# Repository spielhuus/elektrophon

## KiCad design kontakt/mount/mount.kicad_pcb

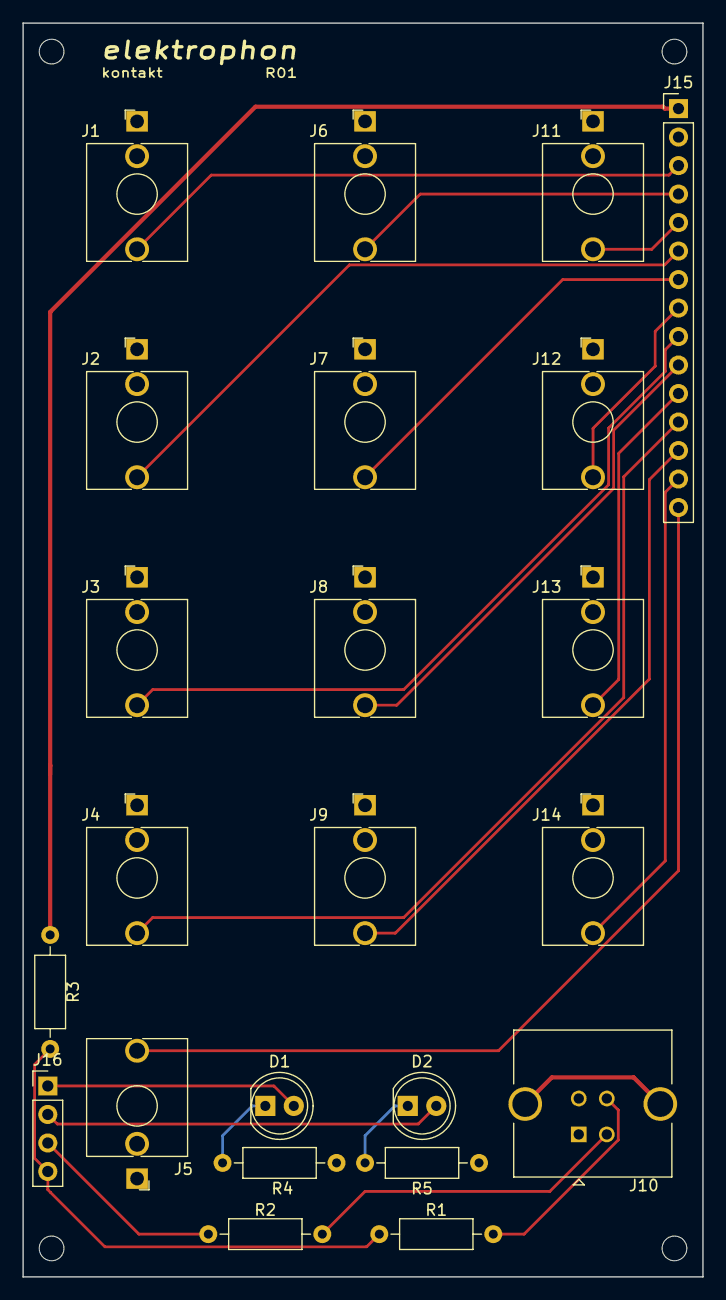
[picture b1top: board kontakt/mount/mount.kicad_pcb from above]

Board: 2 copper layers, 60.6 x 111.8 mm, 27 parts (0 on the bottom side), 23 nets.

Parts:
D1, D2: LED; LED_D5.0mm
H1, H2, H3, H4: MountingHole; MountingHole_2.2mm_M2
J1, J2, J3, J4, J5, J6, J7, J8, J9, J11, J12, J13, J14: INPUT; Jack_3.5mm_WQP-PJ398SM_Vertical
J10: USB_B; USB_B_TE_5787834_Vertical
J15: Conn_01x15_Male; PinHeader_1x15_P2.54mm_Vertical
J16: Conn_01x04_Male; PinHeader_1x04_P2.54mm_Vertical
R1, R2: 20; R_Axial_DIN0207_L6.3mm_D2.5mm_P10.16mm_Horizontal
R3: 1k5; R_Axial_DIN0207_L6.3mm_D2.5mm_P10.16mm_Horizontal
R4, R5: 56; R_Axial_DIN0207_L6.3mm_D2.5mm_P10.16mm_Horizontal

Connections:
+5V: J15.1, R3.2
/PA11: J16.3, R2.1
/PA12: J16.4, R1.1, R3.1
GND: J1.S, J2.S, J3.S, J4.S, J5.S, J6.S, J7.S, J8.S, J9.S, J10.4, J11.S, J12.S, J13.S, J14.S, J15.2, R4.2, R5.2
LED_ACTIVITY: D1.2, J16.1
LED_CONNECT: D2.2, J16.2
unnamed: D1.1, R4.1
unnamed: D2.1, R5.1
unnamed: J10.2, R2.2
unnamed: J10.3, R1.2
Note_1: J1.T, J15.3
Note_2: J6.T, J15.4
Note_3: J11.T, J15.5
OUT_CLOCK: J5.T, J15.15
OUT_TRIGGER_1: J4.T, J15.12
OUT_TRIGGER_2: J9.T, J15.13
OUT_TRIGGER_3: J14.T, J15.14
PITCH_BEND_1: J3.T, J15.9
PITCH_BEND_2: J8.T, J15.10
PITCH_BEND_3: J13.T, J15.11
Velocity_1: J2.T, J15.6
Velocity_2: J7.T, J15.7
Velocity_3: J12.T, J15.8

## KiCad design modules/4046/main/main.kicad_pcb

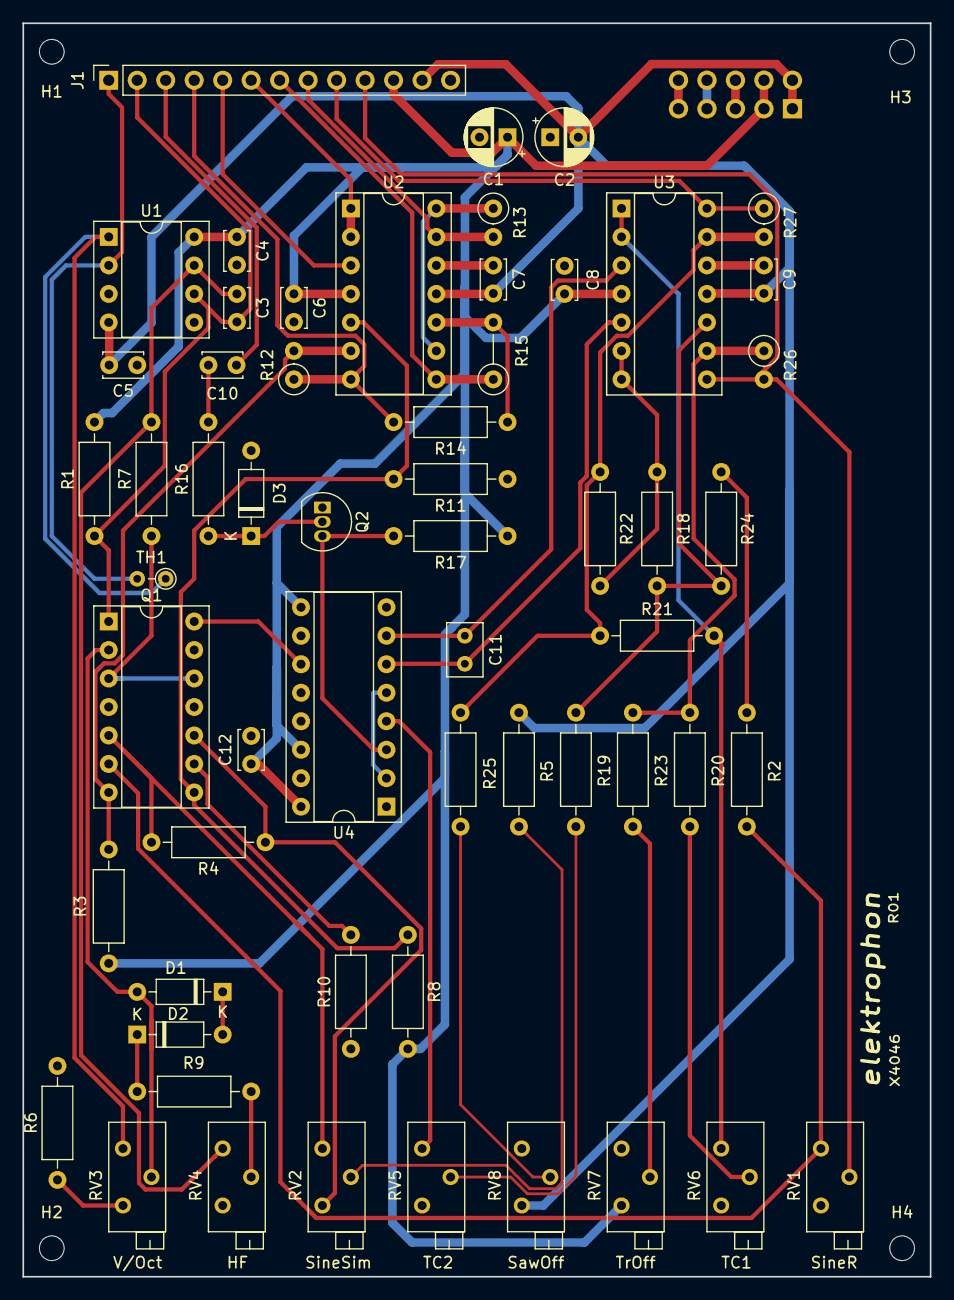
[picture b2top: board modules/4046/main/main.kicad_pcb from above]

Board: 2 copper layers, 80.9 x 111.8 mm, 63 parts (1 on the bottom side), 48 nets.

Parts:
C1, C2: 10u; CP_Radial_D5.0mm_P2.50mm
C3: 100p; C_Disc_D3.4mm_W2.1mm_P2.50mm
C4, C5, C6, C7, C8, C9, C12: 0.1u; C_Disc_D3.4mm_W2.1mm_P2.50mm
C10: 470p; C_Disc_D3.4mm_W2.1mm_P2.50mm
C11: 0.01u (Mylar); C_Rect_L4.6mm_W3.0mm_P2.50mm_MKS02_FKP02
D1, D2, D3: 1N4148; D_DO-35_SOD27_P7.62mm_Horizontal
H1, H2, H3, H4: MountingHole; MountingHole_2.2mm_M2
J1: Conn_01x13_Female; PinSocket_1x13_P2.54mm_Vertical
J2: IDC Header; IDC-Header_2x05_P2.54mm_Vertical
Q1: THAT300; DIP-14_W7.62mm_Socket
Q2: 2N3904; TO-92_Inline
R1: 1M5; R_Axial_DIN0207_L6.3mm_D2.5mm_P10.16mm_Horizontal
R2, R14: 2k2; R_Axial_DIN0207_L6.3mm_D2.5mm_P10.16mm_Horizontal
R3, R8, R9, R11: 10k; R_Axial_DIN0207_L6.3mm_D2.5mm_P10.16mm_Horizontal
R4, R6: 390; R_Axial_DIN0207_L6.3mm_D2.5mm_P10.16mm_Horizontal
R5: 18k; R_Axial_DIN0207_L6.3mm_D2.5mm_P10.16mm_Horizontal
R7: 12k; R_Axial_DIN0207_L6.3mm_D2.5mm_P10.16mm_Horizontal
R10: 2.2k; R_Axial_DIN0207_L6.3mm_D2.5mm_P10.16mm_Horizontal
R12: 10k; R_Axial_DIN0207_L6.3mm_D2.5mm_P2.54mm_Vertical
R13: 120k; R_Axial_DIN0207_L6.3mm_D2.5mm_P2.54mm_Vertical
R15: 2.2M; R_Axial_DIN0207_L6.3mm_D2.5mm_P5.08mm_Vertical
R16, R19: 100k; R_Axial_DIN0207_L6.3mm_D2.5mm_P10.16mm_Horizontal
R17: 4k7; R_Axial_DIN0207_L6.3mm_D2.5mm_P10.16mm_Horizontal
R18, R21, R22: 75k; R_Axial_DIN0207_L6.3mm_D2.5mm_P10.16mm_Horizontal
R20: 33k; R_Axial_DIN0207_L6.3mm_D2.5mm_P10.16mm_Horizontal
R23, R25: 220k; R_Axial_DIN0207_L6.3mm_D2.5mm_P10.16mm_Horizontal
R24: 120k; R_Axial_DIN0207_L6.3mm_D2.5mm_P10.16mm_Horizontal
R26, R27: 100k; R_Axial_DIN0207_L6.3mm_D2.5mm_P2.54mm_Vertical
RV1, RV4, RV5, RV6, RV7, RV8: 100k; Potentiometer_Bourns_3296Z_Horizontal
RV2: 50k; Potentiometer_Bourns_3296Z_Horizontal
RV3: 100; Potentiometer_Bourns_3296Z_Horizontal
TH1: 2k +3500ppm/°C PTC; R_Axial_DIN0204_L3.6mm_D1.6mm_P2.54mm_Vertical
U1: LF442; DIP-8_W7.62mm_Socket
U2, U3: TL074; DIP-14_W7.62mm_Socket
U4: 4046; DIP-16_W7.62mm_Socket

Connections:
+5V: J2.9, J2.10
+15V: C1.1, C4.1, C6.1, C8.1, C12.1, J1.11, J2.3, J2.4, R1.2, R3.2, R8.2, R17.1, RV7.3, U1.8, U2.4, U3.4, U4.9, U4.14, U4.16
-15V: C2.2, C5.2, C7.2, C9.2, J1.12, J2.1, J2.2, R5.1, RV8.3, U1.4, U2.11, U3.11
/CI_1: C11.2, U3.5, U4.6
/CI_2: C11.1, U3.3, U4.7
/CV: Q1.14, U4.11
/EXP_FM: J1.1, TH1.2, U1.2
/HARD_SYNC: C10.2, J1.3
/LIN_FM: C3.2, J1.2, Q1.1, R1.1, U1.6
/PULSE: J1.7, R15.1, U2.8
/PWM: J1.8, R13.2, U2.13
/RAMPOID: J1.6, U2.1, U2.2
/SAW: J1.9, R27.1, U3.14
/SINE: J1.4, R12.1, R14.2, U2.7
/SKEW: J1.5, U2.3
/SYNC: Q2.3, R17.2, U4.3
/TRIANGLE: J1.10, R26.2, RV1.2, U3.8
/VCO_OUT: RV5.1, U4.4
GND: C1.2, C2.1, C4.2, C5.1, C6.2, C7.1, C8.2, C9.1, C12.2, D3.2, J1.13, J2.5, J2.6, J2.7, J2.8, Q1.13, Q2.1, R2.1, R6.2, R10.1, R11.1, R24.1, RV5.3, RV6.3, RV7.1, RV8.1, U1.3, U1.5, U2.12, U3.12, U4.8
unnamed: C3.1, R7.2, RV4.1, U1.7
unnamed: C10.1, R16.2
unnamed: D1.1, D2.2
unnamed: D1.2, Q1.2, RV3.2
unnamed: D2.1, R9.1
unnamed: D3.1, Q2.2, R16.1
unnamed: Q1.5, R4.2, RV2.1
unnamed: Q1.6, R2.2, RV1.1
unnamed: Q1.7, R3.1, R12.2, U2.6
unnamed: Q1.8, R8.1, R11.2, U2.5
unnamed: Q1.9, R10.2
unnamed: Q1.10, R4.1, RV2.3
unnamed: Q1.3, Q1.12, R7.1
unnamed: R5.2, RV2.2
unnamed: R6.1, RV3.3
unnamed: R9.2, RV4.2
unnamed: R13.1, U2.9, U2.14
unnamed: R14.1, R15.2, U2.10
unnamed: R18.1, R22.2, U3.6, U3.7
unnamed: R18.2, R19.2, R24.2, U3.10
unnamed: R19.1, RV5.2
unnamed: R20.1, RV6.2
unnamed: R20.2, R23.1, R26.1, U3.9
unnamed: R21.1, R22.1, R25.1, R27.2, U3.13
unnamed: R21.2, RV6.1, U3.1, U3.2
unnamed: R23.2, RV7.2
unnamed: R25.2, RV8.2
unnamed: RV3.1, TH1.1, U1.1
unnamed: U4.2, U4.5

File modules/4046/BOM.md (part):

## BOM: X4046

### main panel

For the main panel the two integrated circuits the CD4046 and the THAT300 are not so easy to get. The 4046 shall not be from Texas Instruments. It is reported that the chip from TI is hard or impossible to tune. This is sad, becuase this is the part you can find everywhere. You can get the one from National Semiconductor (CD4046), Motorola (MC14046) or Philips (HEF4046). The THAT part is rather expensive, but can be ordered from china. 


| Qty | Reference(s)                  | Value              | Description                                                                                                     | 
|-----|-------------------------------|--------------------|---------------------------------------------------------------------------------------------------------------| 
| 2   | C1, C2                      | 10u                | Electrolytic Capacitors - Radial (D:5.0mm, P:2.50mm)                                                        | 
| 1   | C3                            | 100p               | Ceramic Capacitors (L:4mm, P:2.50mm)                                                                        | 
| 7   | C4, C5, C6, C7, C8, C9, C12 | 0.1u               | Ceramic Capacitors (L:4mm, P:2.50mm)                                                                        | 
| 1   | C10                           | 470p               | Ceramic Capacitors (L:4mm, P:2.50mm)                                                                        | 
| 1   | C11                           | 0.01u              | Capacitor Polyethylene Terephthalate (PET) (L:4.6mm, W:2.5mm, P=2.5mm)                                      | 
| 3   | D1, D2, D3                  | 1N4148             | Diode                                                                                                         | 
| 1   | J1                            | 13 Pins / 1 Row    | Pin Socket Connector (P2.54mm)                                                                                | 
| 1   | J2                            | 10 Pins / 2 Rows   | PCB IDC Socket (P2.54mm, Vertical)                                                                          | 
| 1   | Q1                            | THAT300            | [Matched Transistor Array](https://spielhuus.github.io/elektrophon/datasheet/THAT_300-S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   | 
| 1   | Q2                            | 2N3904             | [Transistors NPN](https://spielhuus.github.io/elektrophon/datasheet/2N3903.pdf)                               | 
| 1   | R1                            | 1M5                | Resistor (L:6.3mm, D:2.5mm)                                                                                 | 
| 1   | R2                            | 2k2                | Resistor (L:6.3mm, D:2.5mm)                                                                                 | 
| 4   | R3, R8, R9, R11             | 10k                | Resistor (L:6.3mm, D:2.5mm)                                                                                 | 
| 2   | R4, R6                      | 390                | Resistor (L:6.3mm, D:2.5mm)                                                                                 | 
| 1   | R5                            | 18k                | Resistor (L:6.3mm, D:2.5mm)                                                                                 | 
| 1   | R7                            | 12k                | Resistor (L:6.3mm, D:2.5mm)                                                                                 | 
| 2   | R10, R14                    | 2.2k               | Resistor (L:6.3mm, D:2.5mm)                                                                                 | 
| 1   | R12                           | 10k                | Resistor (L:6.3mm, D:2.5mm)                                                                                 | 
| 1   | R13                           | 120k               | Resistor (L:6.3mm, D:2.5mm)                                                                                 | 
| 1   | R15                           | 2.2M               | Resistor (L:6.3mm, D:2.5mm)                                                                                 | 
| 2   | R16, R19                    | 100k               | Resistor (L:6.3mm, D:2.5mm)                                                                                 | 
| 1   | R17                           | 4k7                | Resistor (L:6.3mm, D:2.5mm)                                                                                 | 
| 3   | R18, R21, R22               | 75k                | Resistor (L:6.3mm, D:2.5mm)                                                                                 | 
| 1   | R20                           | 33k                | Resistor (L:6.3mm, D:2.5mm)                                                                                 | 
| 2   | R23, R25                    | 220k               | Resistor (L:6.3mm, D:2.5mm)                                                                                 | 
| 1   | R24                           | 120k               | Resistor (L:6.3mm, D:2.5mm)                                                                                 | 
| 2   | R26, R27                    | 100k               | Resistor (L:6.3mm, D:2.5mm)                                                                                 | 
| 2   | RV1, RV4                    | 100k               | Trimpotentiometer (Bourns 3296Z)                                                                              | 
| 1   | RV2                           | 50k                | Trimpotentiometer (Bourns 3296Z)                                                                              | 
| 1   | RV3                           | 100                | Trimpotentiometer (Bourns 3296Z)                                                                              | 
| 3   | RV5, RV6, RV7               | 100k               | Trimpotentiometer (Bourns 3296Z)                                                                              | 
| 1   | RV8                           | 100k             | Trimpotentiometer (Bourns 3296Z)                                                                              | 
| 1   | TH1                           | 2k | PTC (Positive Temperature Coefficient) Thermistors                                                            | 
| 1   | U1                            | LF442              | [Dual Low Power JFETInput Operational Amplifier](https://spielhuus.github.io/elektrophon/datasheet/LF442.pdf) | 
| 2   | U2, U3                      | TL074              | [Low-Noise JFET-Input Operational Amplifiers](https://spielhuus.github.io/elektrophon/datasheet/TL07xx.pdf)   | 
| 1   | U4                            | 4046               | [CMOS Phase Locked Loop](https://spielhuus.github.io/elektrophon/datasheet/cd4046b.pdf)                       | 

### mount panel                                            

| Qty | Reference(s)                              | Value           | Description                                                             | 
|-----|-------------------------------------------|-----------------|-------------------------------------------------------------------------| 
| 1   | C1                                        | 0.22u           | Capacitors Polyethylene Terephthalate (PET) (L4.6mm, W3.0mm, P2.50mm) | 
| 10  | J1, J2, J3, J4, J5, J6, J7, J8, J9, J10 | Mono            | [Audio Jack 3.5mm (PJ398SM, Vertical)](https://www.thonk.co.uk/shop/3-5mm-jacks/)                                  | 
| 1   | J11                                       | 13 Pins / 1 Row | Board Spacer Pin Header,Straight (Single Row, L=15mm, P=2.54mm)       | 
| 5   | R1, R2, R3, R5, R6                      | 100k            | Resistor (L:6.3mm, D:2.5mm)                                           | 
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
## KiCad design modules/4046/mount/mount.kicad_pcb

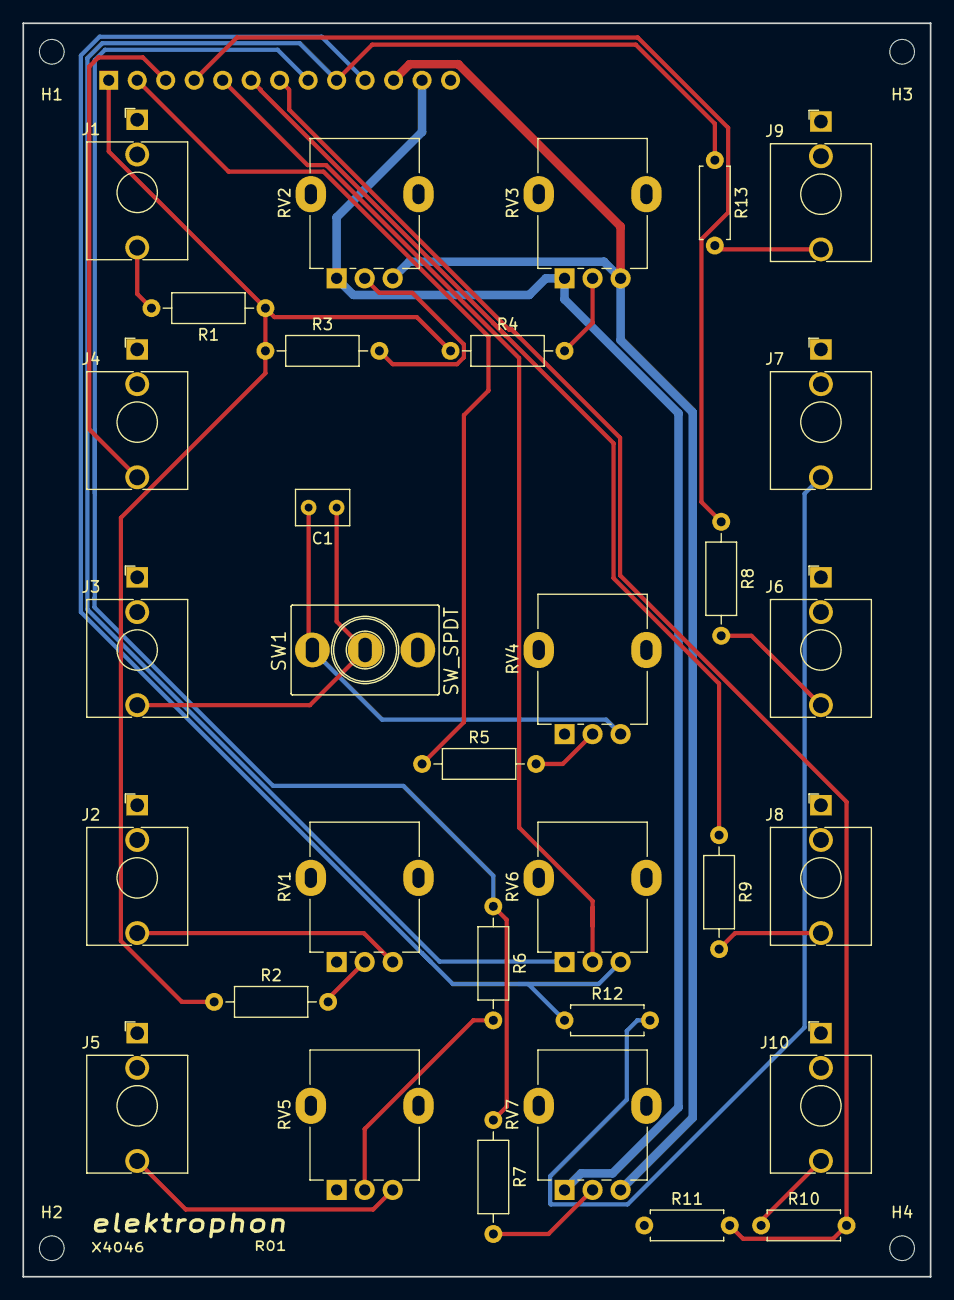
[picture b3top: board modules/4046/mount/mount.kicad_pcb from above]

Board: 2 copper layers, 80.9 x 111.8 mm, 37 parts (1 on the bottom side), 29 nets.

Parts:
C1: 0.22u; C_Rect_L4.6mm_W3.0mm_P2.50mm_MKS02_FKP02
H1, H2, H3, H4: MountingHole; MountingHole_2.2mm_M2
J1, J2, J3, J4, J5, J6, J7, J8, J9, J10: AudioJack2_SwitchT; Jack_3.5mm_QingPu_WQP-PJ398SM_Vertical_CircularHoles
J11: Conn_01x13_Male; PinHeader_1x13_P2.54mm_Vertical
R1, R2, R3, R5, R6: 100k; R_Axial_DIN0207_L6.3mm_D2.5mm_P10.16mm_Horizontal
R4: 3M3; R_Axial_DIN0207_L6.3mm_D2.5mm_P10.16mm_Horizontal
R7: 330k; R_Axial_DIN0207_L6.3mm_D2.5mm_P10.16mm_Horizontal
R8, R9: 1k; R_Axial_DIN0207_L6.3mm_D2.5mm_P10.16mm_Horizontal
R10: 3k; R_Axial_DIN0207_L6.3mm_D2.5mm_P7.62mm_Horizontal
R11: 1k8; R_Axial_DIN0207_L6.3mm_D2.5mm_P7.62mm_Horizontal
R12, R13: 1k; R_Axial_DIN0207_L6.3mm_D2.5mm_P7.62mm_Horizontal
RV1, RV2, RV3, RV4, RV5: 100k; Potentiometer_Alpha_RD901F-40-00D_Single_Vertical
RV6, RV7: 500k; Potentiometer_Alpha_RD901F-40-00D_Single_Vertical
SW1: SW_SPDT; SPDT_KIT

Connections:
+15V: J11.11, RV2.3, RV3.3, RV7.3
-15V: J11.12, RV2.1, RV3.1, RV7.1
/EXP_FM: J11.1, R1.1, R2.1, R3.1, R4.1
/HARD_SYNC: J4.T, J11.3
/LIN_FM: J11.2, R5.1
/PULSE: J11.7, R10.2, R11.2
/PWM: J11.8, R6.1, R7.1
/RAMPOID: J11.6, R9.1
/SAW: J11.9, R13.1, RV6.1
/SINE: J11.4, R8.1
/SKEW: J11.5, RV6.2
/TRIANGLE: J11.10, R12.1, RV6.3
GND: J1.S, J2.S, J3.S, J4.S, J5.S, J6.S, J7.S, J8.S, J9.S, J10.S, J11.13, R11.1, RV1.1, RV4.1, RV5.1
unnamed: C1.1, J3.T, SW1.2
unnamed: C1.2, RV4.3, SW1.1
unnamed: J1.T, R1.2
unnamed: J2.T, RV1.3
unnamed: J5.T, RV5.3
unnamed: J6.T, R8.2
unnamed: J7.T, R12.2
unnamed: J8.T, R9.2
unnamed: J9.T, R13.2
unnamed: J10.T, R10.1
unnamed: R2.2, RV1.2
unnamed: R3.2, RV2.2
unnamed: R4.2, RV3.2
unnamed: R5.2, RV4.2
unnamed: R6.2, RV5.2
unnamed: R7.2, RV7.2

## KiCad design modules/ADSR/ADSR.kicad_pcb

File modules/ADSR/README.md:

## *adsr*

An ADSR creates an envelope for describing the change of audio over time. The envelope can be used for amplitude, filters or pitch. The origin of an 555  based ADSR is published in electronics by Kirschmann, Jacky et al \[[2][2],[3][3],[4][4]\]. This version is directly taken from René Schmitz \[[5][5]\] 'The Fastest Envelope in the West'. For the Attack, Decay and Release the potentiometers are logarithmic. This gives better control over the values. 

## *build*

 The gerber files are part of the release. It should be possible to directly order them from your manufacturer. But check the result on the preview when you order them. The parts are in the [BOM](BOM.md), there are no special parts needed for this build. <br/><br/><br/><br/><br/>

## *calibrate*

No calibration needed.

## *use*

Connect a gate signal to the *IN* of the ADSR and the *OUT* to a VCA or VCF:

**IN** a gate singal for the length of the ADS singal.

**OUT** the final envelope.

**Attack** is the time taken for initial run-up of level from nil to peak, beginning when the key is pressed.

**Decay** is the time taken for the subsequent run down from the attack level to the designated sustain level.

**Sustain** is the level during the main sequence of the sound's duration, until the key is released.

**Release** is the time taken for the level to decay from the sustain level to zero after the key is released.

## *links*

1) Wikipedia: [ADSR][1]
1) [Randall Kirschman, Electronics, Jul.1980][2]
1) [Jonathan Jacky, Electronics, Sept.1980][3]
1) [Örley Gàbor, Electronic Design, Aug. 1980][4]
1) [René Schmitz: The Fastest Envelope in the West][5]
1) [Falstad: Circuit simulation](https://www.falstad.com/circuit/circuitjs.html?cct=$+1+0.000005+382.76258214399064+66+5+43%0A165+288+80+384+80+6+1.7143479604572416e-7%0Ag+-192+208+-192+240+0%0AR+352+48+352+0+0+0+40+15+0+0+0.5%0At+-160+144+-128+144+0+1+0.5716675283568278+0.6312434387200588+100%0Ar+-224+144+-288+144+0+10000%0Ad+-192+208+-192+144+2+default%0Ag+384+240+384+272+0%0Aw+-224+144+-192+144+0%0Aw+-192+144+-160+144+0%0Ar+-128+128+-128+64+0+4700%0Ar+-32+112+-32+48+0+4700%0At+-64+160+-32+160+0+1+-14.940424082116808+0.059575912365064716+100%0Ar+96+160+96+96+0+4700%0At+64+176+96+176+0+1+-14.999999945763738+5.3296261943213006e-8+100%0AR+-128+64+-128+16+0+0+40+15+0+0+0.5%0AR+-32+48+-32+0+0+0+40+15+0+0+0.5%0AR+96+96+96+48+0+0+40+15+0+0+0.5%0Ar+-64+128+-128+128+0+22000%0Ad+16+208+16+144+2+default%0Ag+16+208+16+240+0%0Ar+64+144+16+144+0+10000%0Ac+-32+144+16+144+0+1e-8+14.99999994218561%0Ag+96+192+96+240+0%0Ac+352+272+352+240+0+1e-8+-10.000000000000005%0Ag+352+272+352+320+0%0Aw+96+160+288+176+0%0AR+-288+144+-336+144+0+2+5+5+0+0+0.4%0Aa+592+192+688+192+8+15+-15+1000000+3.502764258031722+3.5027992856743024+100000%0Aw+592+176+592+128+0%0Aw+592+128+688+128+0%0Aw+688+128+688+192+0%0Ap+752+192+832+192+1+0%0Ac+592+288+592+208+0+0.0000022+-3.5027992856743024%0Ag+592+288+592+320+0%0Ad+512+176+560+176+2+default%0A174+432+32+496+64+1+1000000+0.005+release%0Ad+528+112+480+112+2+default%0Aw+288+208+528+208+0%0Aa+288+416+384+416+8+15+-15+1000000+0.06118225697416717+0.06118286879673691+100000%0Aw+288+112+192+112+0%0Aw+192+112+192+400+0%0A174+192+400+256+400+1+10000+0.005+Sustain%0Aw+224+384+288+432+0%0Aw+288+400+288+368+0%0Aw+288+368+384+368+0%0Aw+384+368+384+416+0%0AR+256+336+256+288+0+0+40+15+0+0+0.5%0Ar+256+400+256+336+0+4700%0A174+384+416+448+416+1+1000000+0.024800000000000003+Decay%0Aw+416+320+560+320+0%0Ad+560+208+560+288+2+default%0Ar+416+48+416+112+0+100%0Ar+416+144+416+176+0+100%0Aw+432+32+416+32+0%0Aw+416+32+416+48+0%0Aw+464+64+464+112+0%0Aw+464+112+480+112+0%0A174+416+176+512+144+1+1000000+0.005+Attack%0Ar+560+288+560+320+0+100%0Aw+-64+128+-64+160+0%0Ag+-128+160+-128+208+0%0Aw+64+144+64+176+0%0Ag+-32+176+-32+224+0%0Aw+-32+144+-32+112+0%0Aw+416+112+288+80+0%0Aw+288+80+-32+112+0%0Ar+688+192+752+192+0+1000%0Aw+416+400+416+320+0%0Aw+560+208+592+208+0%0Aw+560+208+528+208+0%0Aw+464+144+464+128+0%0Aw+464+128+512+128+0%0Aw+512+128+512+176+0%0Aw+560+176+560+208+0%0At+784+256+784+304+0+1+-11.557778292162581+0.582583963648529+100%0Ac+800+368+800+336+0+1e-8+-15%0Ag+800+368+800+400+0%0AR+800+304+832+304+0+0+40+15+0+0+0.5%0Aw+800+336+800+304+0%0Ar+720+256+784+256+0+10000%0Aw+688+192+688+256+0%0Aw+720+256+688+256+0%0Ar+752+384+752+320+0+2200%0Aw+752+320+752+304+0%0Aw+752+304+768+304+0%0A162+752+384+752+432+2+default-led+1+0+0+0.01%0Ag+752+432+752+464+0%0Ao+26+64+0+4099+5+0.00078125+0+2+26+3%0Ao+31+64+0+4098+20+0.1+1+1%0A)
---

[1]: https://en.wikipedia.org/wiki/Envelope_(music)
[2]: https://www.yusynth.net/archives/Electronics/R-Kirschman-ADSR-1980.pdf
[3]: https://www.yusynth.net/archives/Electronics/J-Jacky-ADSR-1980.pdf
[4]: https://www.yusynth.net/archives/ElectronicDesign/O-Gabor-ADSR-1980.pdf
[5]: https://www.schmitzbits.de/adsr.html

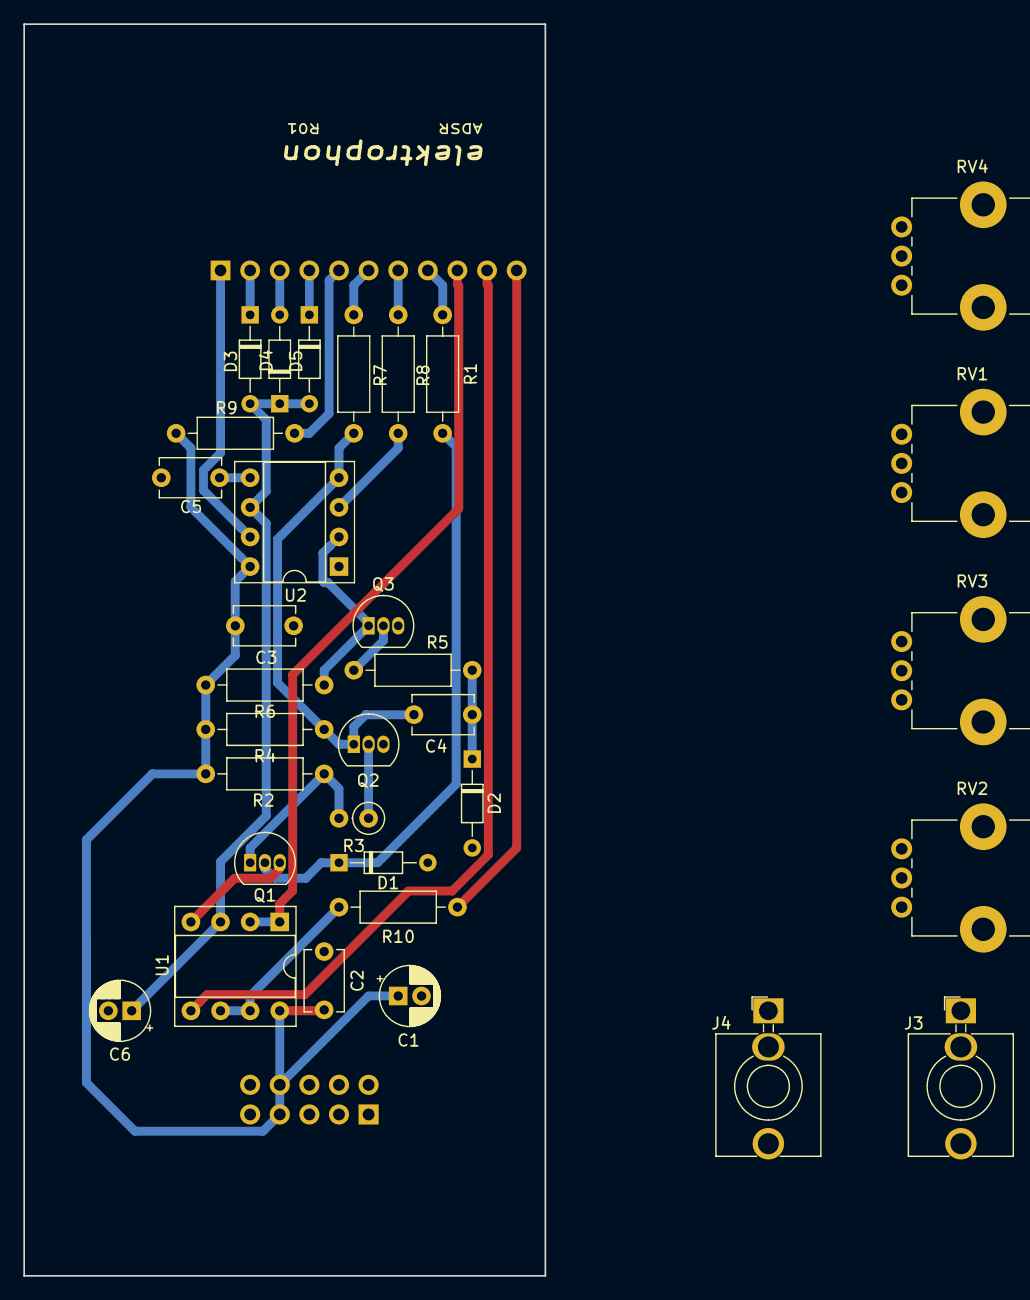
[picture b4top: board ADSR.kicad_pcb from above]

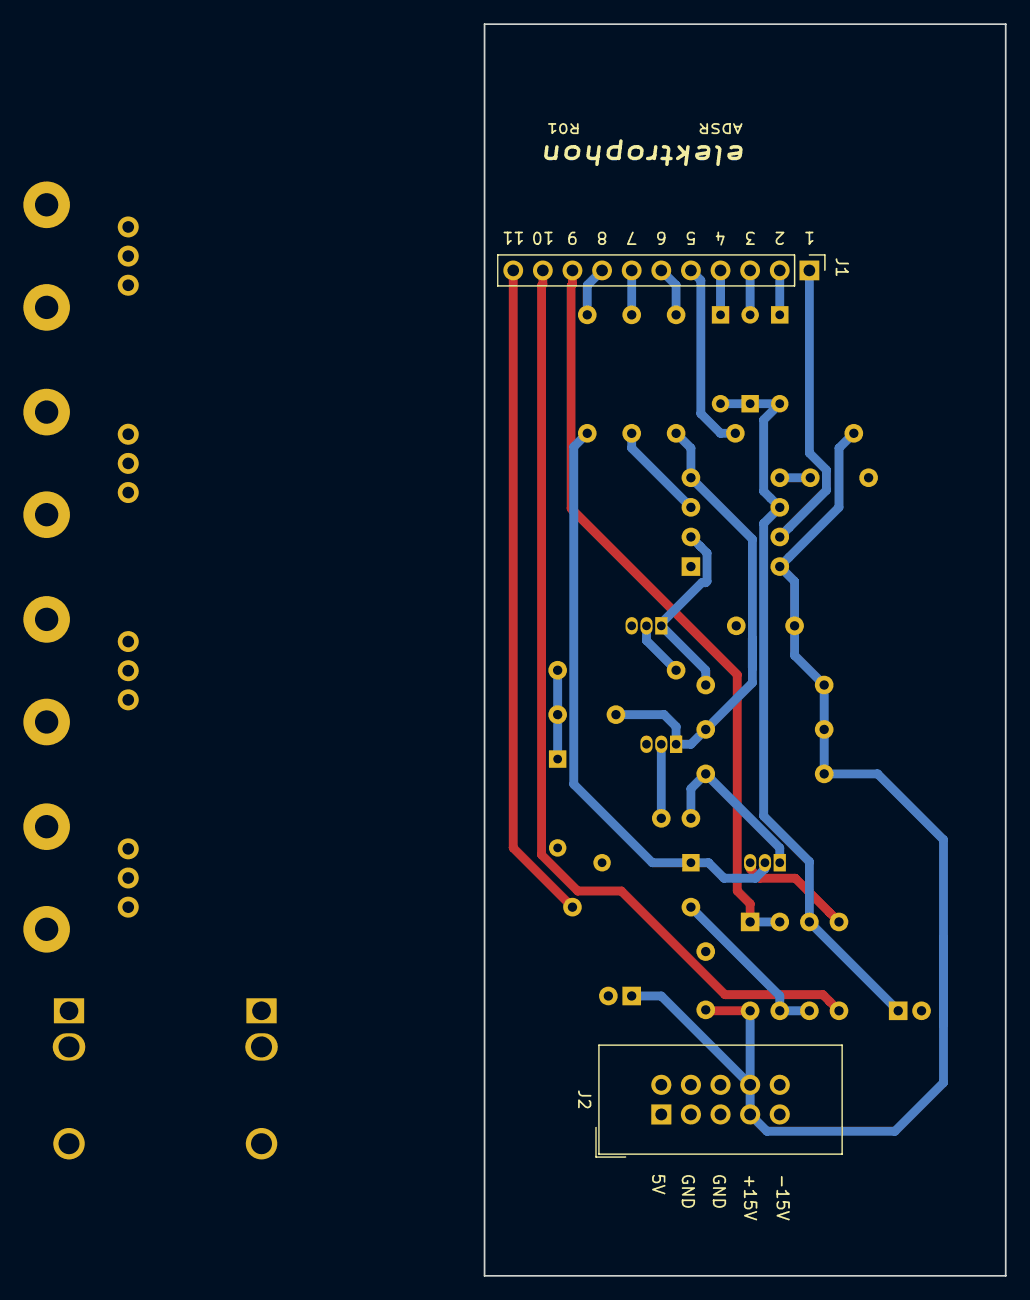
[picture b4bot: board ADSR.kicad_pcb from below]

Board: 2 copper layers, 44.7 x 107.3 mm, 34 parts (2 on the bottom side), 25 nets.

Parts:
C1: 22u; CP_Radial_D5.0mm_P2.00mm
C2, C3: 0.1u; C_Disc_D5.1mm_W3.2mm_P5.00mm
C4, C5: 10n; C_Disc_D5.1mm_W3.2mm_P5.00mm
C6: 4u7; CP_Radial_D5.0mm_P2.00mm
D1, D2, D3, D4, D5: D; D_DO-34_SOD68_P7.62mm_Horizontal
J1: Panel; PinHeader_1x11_P2.54mm_Vertical
J2: Power; IDC-Header_2x05_P2.54mm_Vertical
J3, J4: AudioJack3; Jack_3.5mm_QingPu_WQP-PJ398SM_Vertical_CircularHoles
Q1, Q2, Q3: BC547; TO-92_Inline
R1, R5: 10k; R_Axial_DIN0207_L6.3mm_D2.5mm_P10.16mm_Horizontal
R2, R4, R6, R9: 4k7; R_Axial_DIN0207_L6.3mm_D2.5mm_P10.16mm_Horizontal
R3: 22k; R_Axial_DIN0207_L6.3mm_D2.5mm_P2.54mm_Vertical
R7, R8, R10: 100; R_Axial_DIN0207_L6.3mm_D2.5mm_P10.16mm_Horizontal
RV1: 10k; Potentiometer_Bourns_PTV09A-1_Single_Vertical
RV2, RV3, RV4: 1M; Potentiometer_Bourns_PTV09A-1_Single_Vertical
U1: LM358; DIP-8_W7.62mm_Socket
U2: ICM7555; DIP-8_W7.62mm_Socket

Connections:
+5V: J2.1, J2.2
+15V: C1.1, C2.2, C3.1, J2.7, J2.8, R2.1, R4.1, R6.1, R9.2, U1.8, U2.8
Attack_1: J1.7, R8.1, RV3.2, RV3.3
Attack_2: D4.2, J1.3, RV3.1
Decay_1: D5.1, J1.4, RV4.3
Decay_2: J1.11, R10.2, RV4.1, RV4.2
GND: C1.2, C2.1, C3.2, C5.1, C6.2, D1.2, D2.2, J2.3, J2.4, J2.5, J2.6, Q1.3, Q2.3, Q3.3, U1.4, U2.1
IN: J1.8, R1.2
unnamed: C4.1, D2.1, R5.2
unnamed: C4.2, Q2.1, R4.2, R7.2, U2.4
unnamed: C5.2, U2.5
unnamed: C6.1, D3.2, D4.1, D5.2, U1.3, U2.6
unnamed: D1.1, Q1.2, R1.1
unnamed: Q1.1, R2.2, R3.2
unnamed: Q2.2, R3.1
unnamed: Q3.1, R6.2, U2.2
unnamed: Q3.2, R5.1
unnamed: R8.2, U2.3
unnamed: R10.1, U1.6, U1.7
OUT: J1.9, U1.1, U1.2
Release_1: J1.6, R7.1, RV2.2, RV2.3
Release_2: D3.1, J1.2, RV2.1
Sustain_1: J1.5, R9.1, RV1.1
Sustain_2: J1.10, RV1.2, U1.5
Sustain_3: J1.1, RV1.3, U2.7

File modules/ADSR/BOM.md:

## ADSR: BOM

### main panel

|Qty|Reference(s)      |Value  |Footprint                                                                        |
|---|------------------|-------|---------------------------------------------------------------------------------|
|1  |C1                |10u    |Electrolytic Capacitors - Radial (D:5.0mm, P:2.50mm)                             |
|2  |C2, C3            |0.1u   |Ceramic Capacitors (L:4mm, P:2.50mm)                                             |
|2  |C4, C5            |10n    |Ceramic Capacitors (L:4mm, P:2.50mm)                                             |
|1  |C6                |4u7    |Ceramic Capacitors (L:4mm, P:2.50mm)                                             |
|1  |C7                |100n   |Ceramic Capacitors (L:4mm, P:2.50mm)                                             |
|5  |D1, D2, D3, D4, D5|D      |Diode                                                                            |
|1  |D6                |LED    |LED 5mm (color of your choice)                                                   |
|1  |J1                |IN     |[Audio Jack 3.5mm (PJ398SM, Vertical)](https://www.thonk.co.uk/shop/3-5mm-jacks/)|
|1  |J2                |Power  |Connector_IDC:IDC-Header_2x05_P2.54mm_Vertical                                   |
|1  |J3                |OUT    |[Audio Jack 3.5mm (PJ398SM, Vertical)](https://www.thonk.co.uk/shop/3-5mm-jacks/)|
|4  |Q1, Q2, Q3, Q4    |BC547  |NPN Epitaxial Silicon Transistor                                                 |
|3  |R1, R5, R11       |10k    |Resistor (L:6.3mm, D:2.5mm)                                                      |
|4  |R2, R4, R6, R9    |4k7    |Resistor (L:6.3mm, D:2.5mm)                                                      |
|1  |R3                |22k    |Resistor (L:6.3mm, D:2.5mm)                                                      |
|3  |R7, R8, R10       |100    |Resistor (L:6.3mm, D:2.5mm)                                                      |
|1  |R12               |2k2    |Resistor (L:6.3mm, D:2.5mm)                                                      |
|1  |R13               |1k     |Resistor (L:6.3mm, D:2.5mm)                                                      |
|1  |RV1               |10k    |Potentiometer Alpha RD901F-40-00D                                                |
|3  |RV2, RV3, RV4     |1M     |Potentiometer Alpha RD901F-40-00D                                                |
|1  |U1                |LM358  |Operational Amplifiers - Op Amps                                                 |
|1  |U2                |ICM7555|Timer                                                                            |

### misc material

| Qty | Reference(s)             | Value              | Description | 
|-----|--------------------------|--------------------|-------------|
| 4   |                        | 6.35mm              | Potentiometer Knobs, colors of your choice   |

---
[![CC BY-SA](https://licensebuttons.net/l/by-sa/3.0/88x31.png)](https://c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

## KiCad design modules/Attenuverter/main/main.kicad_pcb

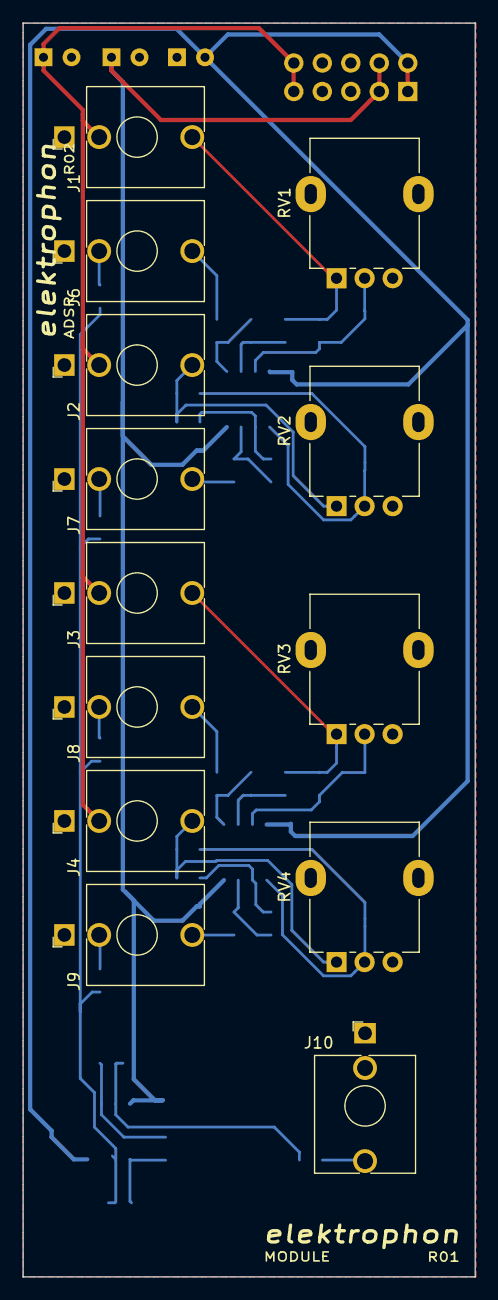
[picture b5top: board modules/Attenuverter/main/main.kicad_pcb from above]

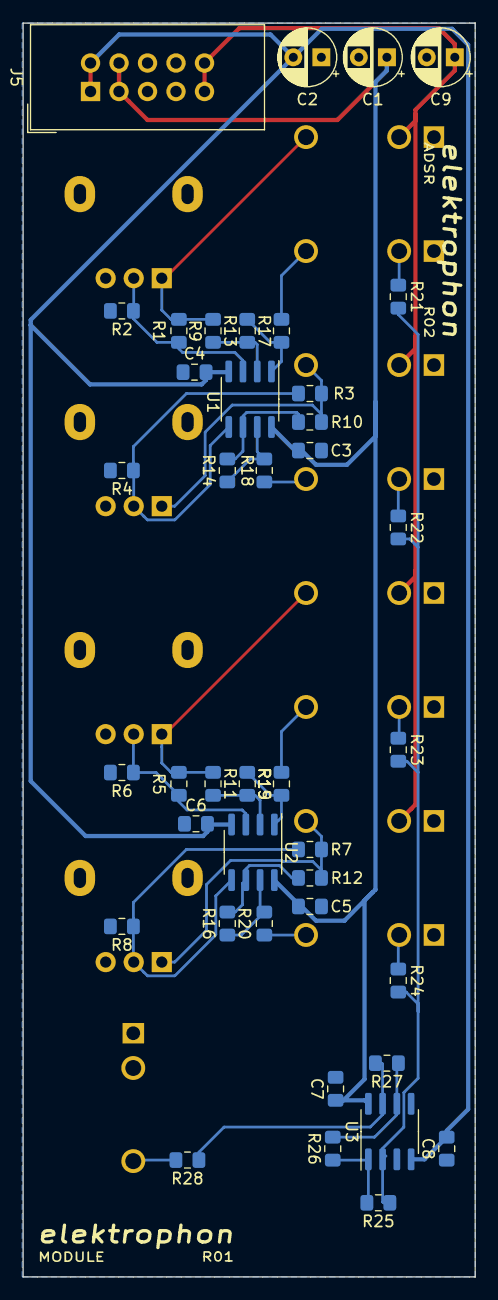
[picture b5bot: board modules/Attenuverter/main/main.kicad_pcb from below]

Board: 2 copper layers, 40.3 x 111.8 mm, 54 parts (41 on the bottom side), 33 nets.

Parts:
C1, C2, C9: 10u; CP_Radial_D5.0mm_P2.50mm
C3, C4, C5, C6, C7, C8: 0.1u; C_0805_2012Metric_Pad1.15x1.40mm_HandSolder
J1, J2, J3, J4: IN; Jack_3.5mm_WQP-PJ398SM_Vertical
J5: IDC Header; IDC-Header_2x05_P2.54mm_Vertical
J6, J7, J8, J9, J10: OUT; Jack_3.5mm_WQP-PJ398SM_Vertical
R1, R2, R3, R4, R5, R6, R7, R8: 47k; R_0805_2012Metric_Pad1.15x1.40mm_HandSolder
R9, R10, R11, R12, R13, R14, R15, R16, R21, R22, R23, R24, R25, R26, R27: 100k; R_0805_2012Metric_Pad1.15x1.40mm_HandSolder
R17, R18, R19, R20, R28: 1k; R_0805_2012Metric_Pad1.15x1.40mm_HandSolder
RV1, RV2, RV3, RV4: 100k; Potentiometer_Alpha_RD901F-40-00D_Single_Vertical
U1, U2, U3: OPA2134; SOIC-8_3.9x4.9mm_P1.27mm

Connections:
+5V: C9.1, J1.TN, J2.TN, J3.TN, J4.TN, J5.9, J5.10
+15V: C1.1, C3.1, C5.1, C7.1, J5.3, J5.4, U1.8, U2.8, U3.8
-15V: C2.2, C4.2, C6.2, C8.2, J5.1, J5.2, U1.4, U2.4, U3.4
/MIX_1: J6.TN, R21.1
/MIX_2: J7.TN, R22.1
/MIX_3: J8.TN, R23.1
/MIX_4: J9.TN, R24.1
GND: C1.2, C2.1, C3.2, C4.1, C5.2, C6.1, C7.2, C8.1, C9.2, J1.S, J2.S, J3.S, J4.S, J5.5, J5.6, J5.7, J5.8, J6.S, J7.S, J8.S, J9.S, J10.S, R2.2, R4.2, R6.2, R8.2, RV1.3, RV2.3, RV3.3, RV4.3, U3.3, U3.5
unnamed: J1.T, R1.1, R9.2, RV1.1
unnamed: J2.T, R3.1, R10.2, RV2.1
unnamed: J3.T, R5.1, R11.2, RV3.1
unnamed: J4.T, R7.1, R12.2, RV4.1
unnamed: J6.T, R17.2
unnamed: J7.T, R18.2
unnamed: J8.T, R19.2
unnamed: J9.T, R20.2
unnamed: J10.T, R28.2
unnamed: R1.2, R2.1, RV1.2, U1.3
unnamed: R3.2, R4.1, RV2.2, U1.5
unnamed: R5.2, R6.1, RV3.2, U2.3
unnamed: R7.2, R8.1, RV4.2, U2.5
unnamed: R10.1, R14.2, U1.6
unnamed: R11.1, R15.2, U2.2
unnamed: R12.1, R16.2, U2.6
unnamed: R13.1, R17.1, U1.1
unnamed: R9.1, R13.2, U1.2
unnamed: R14.1, R18.1, U1.7
unnamed: R15.1, R19.1, U2.1
unnamed: R16.1, R20.1, U2.7
unnamed: R21.2, R22.2, R23.2, R24.2, R25.1, U3.2
unnamed: R25.2, R26.1, U3.1
unnamed: R26.2, R27.1, U3.6
unnamed: R27.2, R28.1, U3.7

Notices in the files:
modules/4046/BOM.md:
[CC BY-SA](https://licensebuttons.net/l/by-sa/3.0/88x31.png)](https://creativecommons.org/licenses/by-sa/4.0/)
modules/4046/main/main.kicad_pcb:
License CC BY 4.0 - Attribution 4.0 International
